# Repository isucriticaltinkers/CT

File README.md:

# CT
Critical Tinkers Code Repository

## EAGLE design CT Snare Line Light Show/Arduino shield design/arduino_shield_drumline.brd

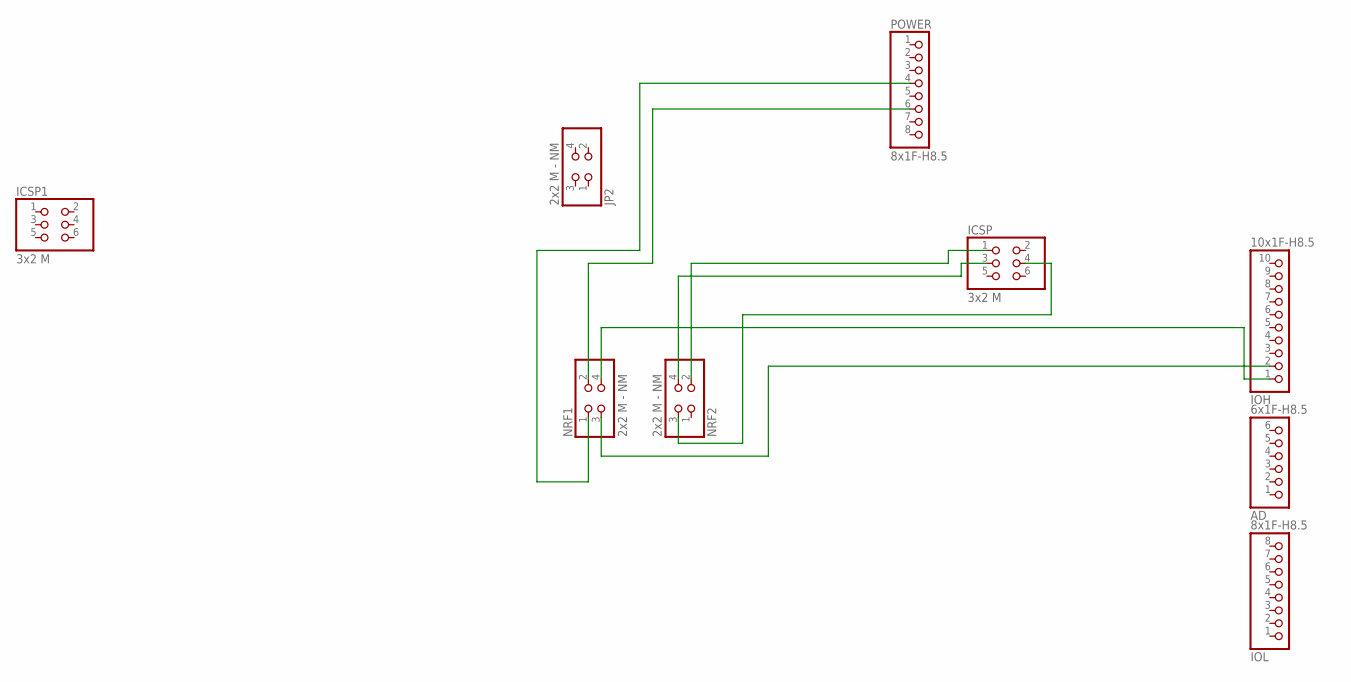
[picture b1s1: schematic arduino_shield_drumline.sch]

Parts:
AD: 6x1F-H8.5; 1X06
ICSP, ICSP1: 3x2 M; 2X03
IOH: 10x1F-H8.5; 1X10
IOL: 8x1F-H8.5; 1X08
JP2: 2x2 M - NM; 2X02
NRF1, NRF2: 2x2 M - NM; 2X02
POWER: 8x1F-H8.5; 1X08

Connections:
unnamed: NRF1.1, POWER.4
unnamed: NRF1.2, POWER.6
unnamed: IOH.1, NRF1.4
unnamed: IOH.2, NRF1.3
unnamed: ICSP.3, NRF2.4
unnamed: ICSP.1, NRF2.2
unnamed: ICSP.4, NRF2.3

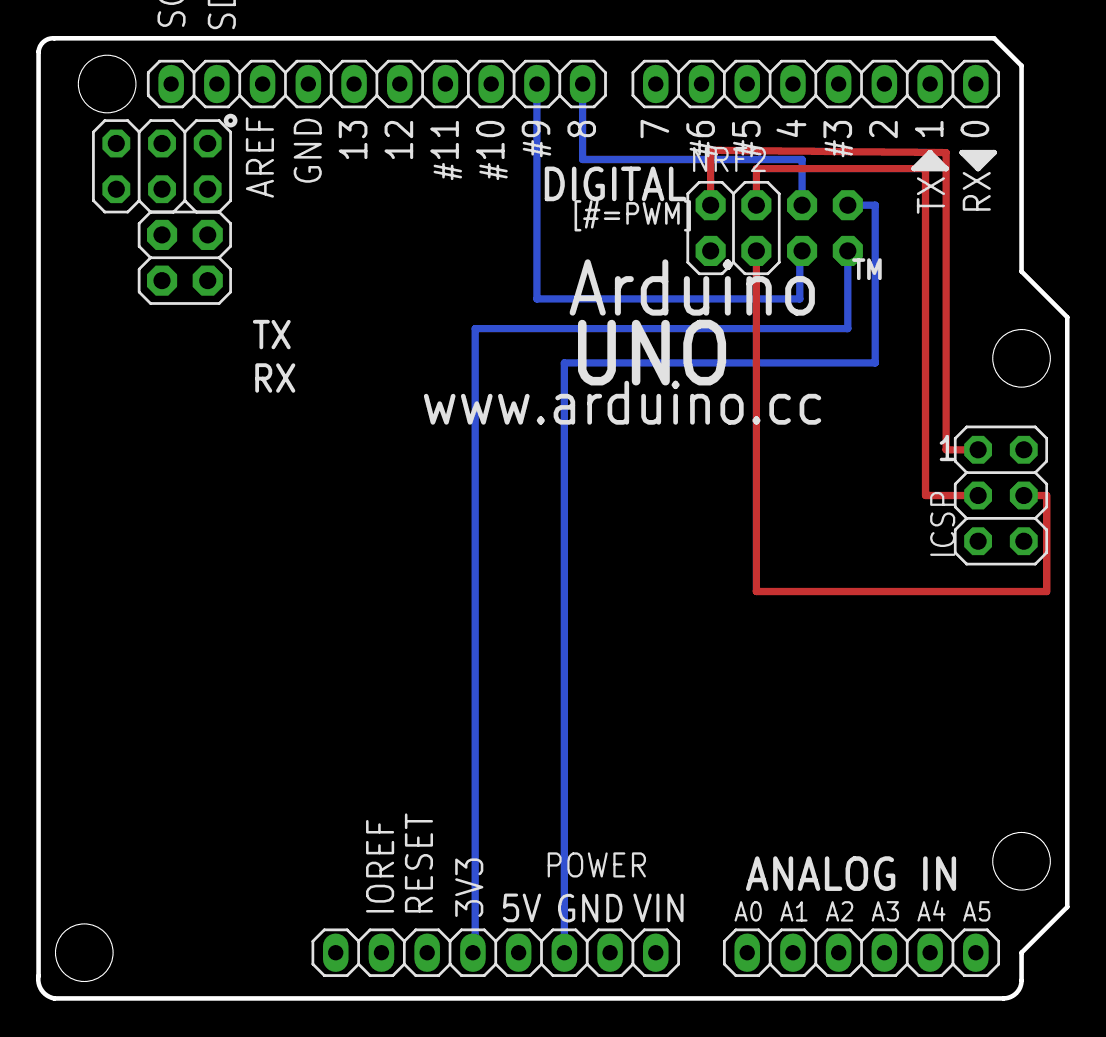
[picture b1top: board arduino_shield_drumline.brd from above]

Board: 2 copper layers, 57.2 x 53.3 mm, 9 parts (1 on the bottom side), 7 nets.

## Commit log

2017-02-20 Bass Drums for Band Light Show
    Version 2.3
2017-02-20 Snare_Line_Band_Light_Show
    Snare Line
